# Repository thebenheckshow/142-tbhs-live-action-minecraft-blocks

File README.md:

# 142-tbhs-live-action-minecraft-blocks

Ben is inspired by Minecraft and how it's possible to create logic gates within the game. He decides to make real-world versions of the blocks, switches, torches, and redstone needed to build the gates. He aims to create a fun, hands-on way to learn about logic gates. In part onen of the series he goes over the plan and builds the red stone blocks.

In the second part of the series, Ben continues to build real-world versions of Minecraft blocks, switches, torches, and more. Each block will have a role in creating logic gates just like in the Minecraft game. Ben shows you how he builds each kind of block and does some tests along the way. Once all the pieces are working, he tries building some live action logic gates.

Episode 142: Ben's Live Action Minecraft Blocks Part 1 Episode
	http://www.element14.com/community/docs/DOC-69281/l/episode-142-bens-live-action-minecraft-blocks-part-1-episode

Episode 143: Ben's Live Action Minecraft Blocks Part 2 Episode
	http://www.element14.com/community/docs/DOC-69282/l/episode-143-bens-live-action-minecraft-blocks-part-2-episode

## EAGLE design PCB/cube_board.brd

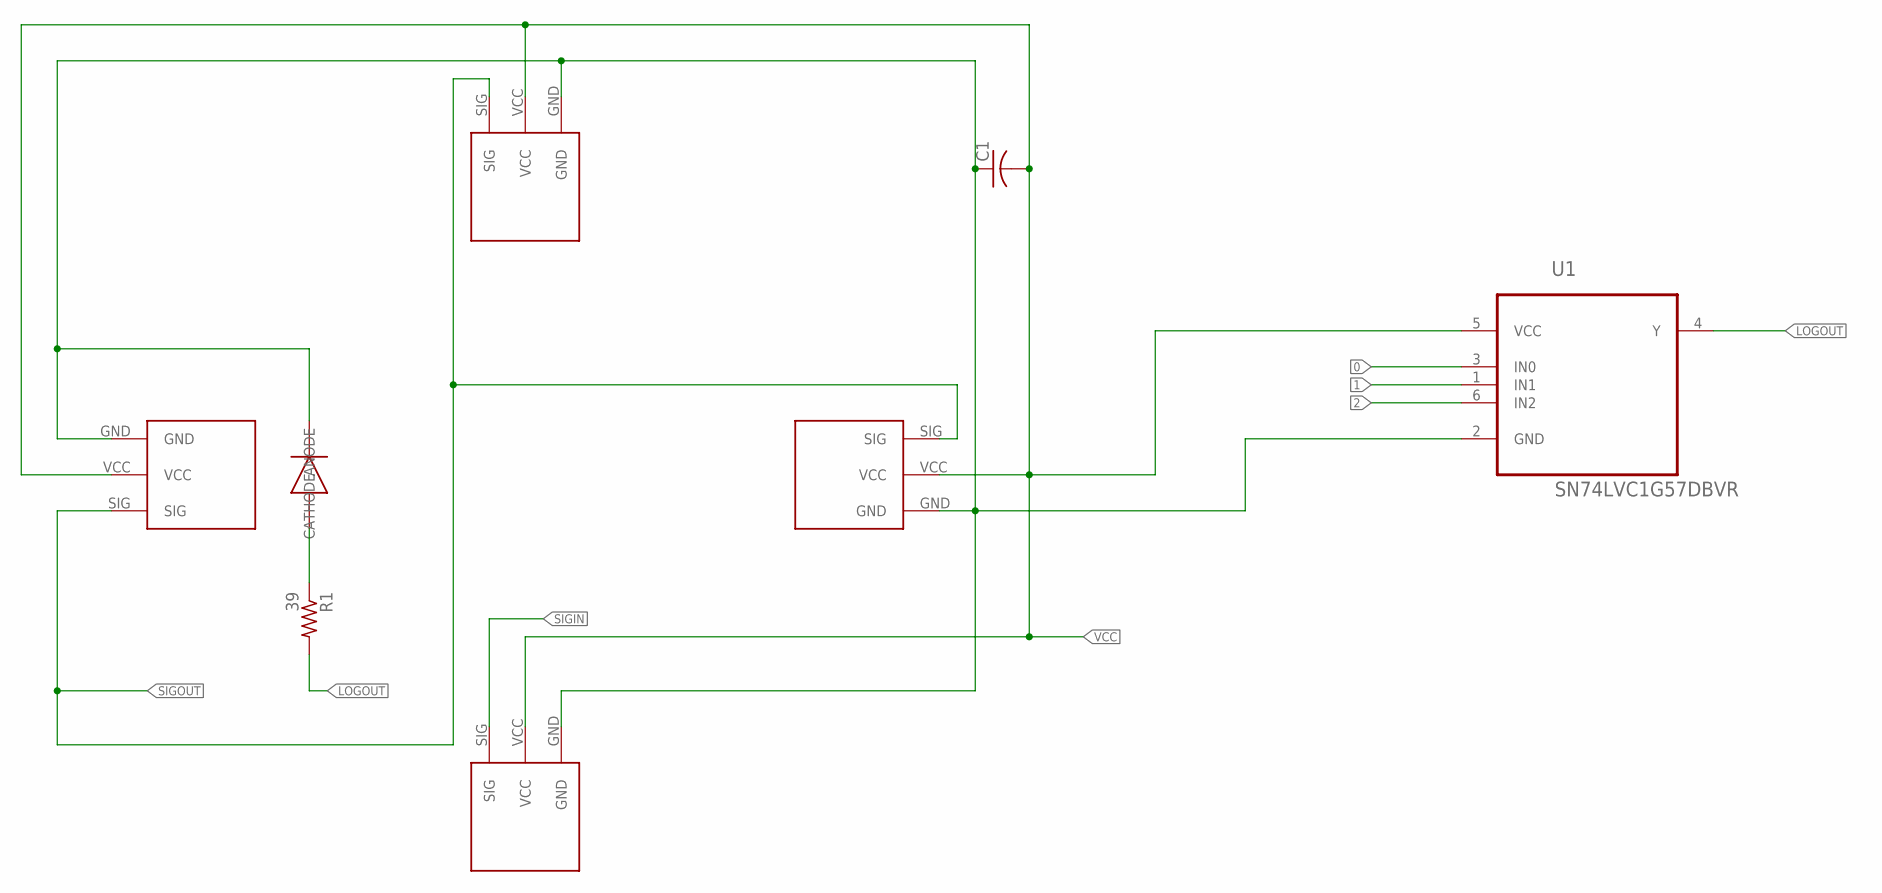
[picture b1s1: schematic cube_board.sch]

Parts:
C1: C-USC0805; C0805
LED: SMD_LED
R1: 39; M1206
U1: SN74LVC1G57DBVR; SOT95P280X145-6N
U$2, U$3, U$4, U$5: CUBE_CONNECTOR

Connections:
0: U1.3 (IN0)
1: U1.1 (IN1)
2: U1.6 (IN2)
LOGOUT: R1.2, U1.4 (Y)
unnamed: LED.ANODE, R1.1
unnamed: C1.1, LED.CATHODE, U1.2 (GND), U$2.GND, U$3.GND, U$4.GND, U$5.GND
SIGIN: U$2.SIG
SIGOUT: U$3.SIG, U$4.SIG, U$5.SIG
VCC: C1.2, U1.5 (VCC), U$2.VCC, U$3.VCC, U$4.VCC, U$5.VCC

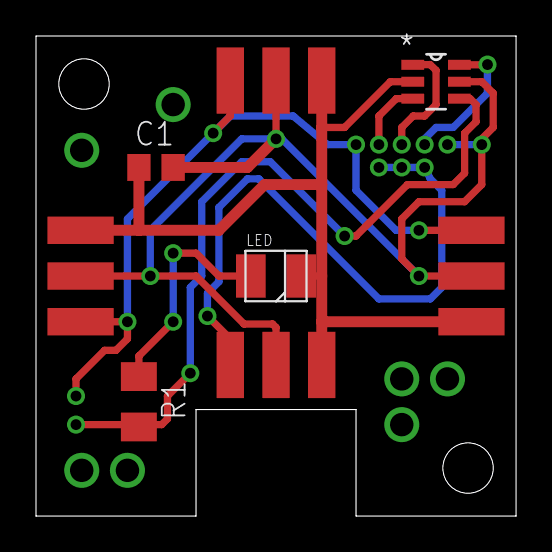
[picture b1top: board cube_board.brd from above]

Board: 2 copper layers, 26.7 x 26.7 mm, 8 parts (0 on the bottom side), 5 nets.
